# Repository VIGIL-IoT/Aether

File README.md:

# Aether

Aether is an open-source learning project with a browser-based model of two nRF24 channel selectors and a proposed KiCad carrier for an ESP32 DevKitC V4 with two nRF24 breakouts.

## Project status

| Part | Status |
| --- | --- |
| Browser simulator | Implemented. Deterministically models channel selection; emits no RF. |
| KiCad carrier R1 | Schematic and two-layer board are present and pass the recorded KiCad ERC/DRC checks. The design is unbuilt and has not been fit-checked. |
| ESP32 firmware | Legacy sketches are present but are not verified against the R1 carrier or validated on hardware. Some sketches contain RF transmission routines. |
| RF experiments | Proposals only. No measurement data or experiment results are checked in. |

The live simulator is [aether-nrf-sim.vercel.app](https://aether-nrf-sim.vercel.app/). It is the Aether app; vigil-lyart-iota.vercel.app is unrelated.

## What the simulator does

- Shows two model radios selecting among RF_CH values 0–125.
- Maps each value to a modelled centre frequency using 2400 MHz + RF_CH.
- Provides sequential, seeded-random, and fixed-offset selection modes.
- Tracks modelled visits and elapsed simulated time.
- Marks selected Wi-Fi and Bluetooth LE frequencies for reference.

The simulator does not transmit RF, scan the spectrum, generate Wi-Fi or BLE traffic, simulate packets, or measure RSSI, power, temperature, or battery state. Its outputs are deterministic software-model results.

## Architecture

```mermaid
flowchart LR
    Host["Vercel static host<br/>web/dist"] -->|static assets| UI["React browser interface<br/>controls · spectrum · history"]
    UI -->|actions| Store["In-memory simulation store"]
    Timer["Browser interval"] -->|step() while running| Store
    Store -->|current state| Model["Pure deterministic RF_CH model"]
    Model -->|next state| Store
    Store -->|subscribed snapshots| UI
    subgraph Separate["Separate repository artifacts · no runtime link"]
        Carrier["KiCad carrier R1<br/>unbuilt proposal"]
        Firmware["Legacy ESP32 firmware<br/>unvalidated"]
    end
```

See the [detailed current-system architecture](docs/architecture.md) for the component boundary and validation limits.

## Run the simulator

Requires Node.js 24 (see [.nvmrc](.nvmrc) and `web/package.json`).

    cd web
    npm ci
    npm run dev

From `web/`, run the one-command verification path:

    npm run verify

See [web/README.md](web/README.md) for controls and [docs/setup-guide.md](docs/setup-guide.md) for setup details.

For the algorithm, test method, and limits, see [methodology](docs/methodology.md). Dependency audits and on-demand SBOM generation are documented in [dependency management](docs/dependency-management.md).

## Hardware

The current carrier proposal is in [hardware/kicad/aether-carrier-r1](hardware/kicad/aether-carrier-r1/). It is powered through the ESP32 DevKit's USB input and routes its 3V3/GND and GPIO signals to two radio sockets. It has no battery, charger, USB connector, regulator, or external antenna connector.

Open the KiCad project file in that folder. Review its [README](hardware/kicad/aether-carrier-r1/README.md) and BOM before considering fabrication. The board assumes specific mating-board dimensions and pin numbering; verify the actual parts and mechanical clearances before ordering. ERC/DRC results do not establish physical fit, RF performance, or regulatory compliance.

The older files under [hardware/schematics](hardware/schematics/) and the older PCB notes are retained as legacy material and are not the R1 design.

## Safety and firmware status

The browser simulator is software-only. The legacy firmware is a separate, unvalidated codebase; it has not been reconciled with the R1 pin map, tested on hardware, or reviewed for deployment. Do not treat its presence as evidence of a safe or working radio. Review [docs/legal-and-safety.md](docs/legal-and-safety.md) before handling transmitter-capable hardware.

## Documentation

- [Documentation hub](docs/index.md)
- [Current architecture](docs/architecture.md)
- [Project scope and requirements](docs/project-scope.md)
- [Implementation methodology](docs/methodology.md)
- [Research gap and evidence needs](docs/research-gap.md)
- [Research sources](docs/research-sources.md)
- [Engineering evidence, assumptions, and FMEA-lite](docs/engineering-evidence.md)
- [Hardware references](docs/hardware-references.md)
- [Compatibility and contracts](docs/compatibility-and-contracts.md)
- [AI skills reference](docs/AI_SKILLS_REFERENCE.md)
- [Limitations](docs/limitations.md)
- [Traceability](docs/traceability.md)
- [Validation record](docs/testing-methodology.md)
- [Repository audit](docs/REPOSITORY_AUDIT.md)
- [Dependency management](docs/dependency-management.md)
- [KiCad carrier R1](hardware/kicad/aether-carrier-r1/README.md)
- [Experiments: proposals and status](experiments/README.md)
- [Security policy](SECURITY.md)
- [Web verification workflow](.github/workflows/verify-web.yml)

## Repository layout

    docs/          Project, architecture, setup, and validation documentation
    experiments/   Unexecuted experiment proposals; no result data
    firmware/      Legacy ESP32/nRF24 sketches, unvalidated against carrier R1
    hardware/      Current KiCad carrier and legacy hardware material
    web/           React/TypeScript simulator, model tests, and Vite/Vercel config

## Licensing

The repository contains a GPL-3.0 license and a CERN-OHL-S v2 hardware license. Check the relevant license file and file headers for the material you use. Firmware provenance is not fully audited; see [firmware/CHANGES.md](firmware/CHANGES.md). No license terms have been changed as part of this status correction.

## Contributing

See [CONTRIBUTING.md](CONTRIBUTING.md). Contributions should preserve the distinction between simulated output, unverified firmware, and measured hardware results.

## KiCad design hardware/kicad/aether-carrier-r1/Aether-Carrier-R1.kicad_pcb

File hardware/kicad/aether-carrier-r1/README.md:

# Aether Carrier R1

A two-layer socket carrier for one ESP32-DevKitC V4 and two nRF24L01+ breakout modules. This is a KiCad design proposal; it has not been fabricated, assembled, or physically fit-checked.

See [hardware references](../../../docs/hardware-references.md) for manufacturer constraints and [engineering evidence](../../../docs/engineering-evidence.md) for assumptions and failure modes. Exact mating-board and breakout module MPNs are not recorded.

## Files

- `Aether-Carrier-R1.kicad_pro`: KiCad project settings
- `Aether-Carrier-R1.kicad_sch`: electrical schematic
- `Aether-Carrier-R1.kicad_pcb`: routed carrier board
- `Aether.pretty/`: custom socket footprints
- `BOM.csv`: connector, passive, and mating-module list

Open the project with KiCad 10 or later. The custom footprints are loaded from the project-local `Aether.pretty` library.

## Electrical design

The carrier is powered through the ESP32 DevKit's own USB connector. The DevKit's 3V3 pin supplies both radio sockets. The carrier contains no battery, charger, USB connector, or voltage regulator. Do not power the carrier by applying an external supply to its 3V3 rail while the DevKit is connected to USB. Espressif documents the DevKitC V4 power-input options and their mutual-exclusion requirements in its [official guide](https://docs.espressif.com/projects/esp-dev-kits/en/latest/esp32/esp32-devkitc/user_guide.html).

| Radio | Bus | SCK | MOSI | MISO | CE | CSN |
|---|---|---:|---:|---:|---:|---:|
| J2 | HSPI | GPIO25 | GPIO26 | GPIO35 | GPIO32 | GPIO27 |
| J3 | VSPI | GPIO18 | GPIO23 | GPIO19 | GPIO22 | GPIO21 |

J1 uses an ESP32-DevKitC V4 2×19 header viewed from above with USB at the top: odd-numbered pins are on the left and even-numbered pins are on the right. Unused DevKit pins have explicit no-connect markers. J1 pins 1, 2, 14, and 27 provide 3V3/GND connections as shown in the schematic.

J2 and J3 use the common numbered nRF24L01+ 2×4 module header:

| Pin | Signal | Pin | Signal |
|---:|---|---:|---|
| 1 | GND | 2 | VCC (3V3) |
| 3 | CE | 4 | CSN |
| 5 | SCK | 6 | MOSI |
| 7 | MISO | 8 | IRQ (NC) |

The socket footprints mark pin 1 with a square pad. Module and adapter vendors can change the board layout or labels; verify the specific mating module's pinout and orientation before inserting it or applying power. Pin 8 IRQ is intentionally unconnected because the carrier's current signal map does not use radio interrupts. The [RF24 library documentation](https://github.com/nRF24/RF24/blob/master/docs/main_page.md) lists the conventional module header signals.

C1/C3 are 10 µF 1206 capacitors and C2/C4 are 100 nF 0805 capacitors, one pair beside each radio socket. Their values and placement are design choices for this untested prototype, not measured power-integrity results.

## Board and fabrication notes

- Outline: 73.66 × 71.12 mm
- Two copper layers; bottom GND zone and local ground stitching
- Signal tracks: 0.30 mm; 3V3/GND tracks: 0.50 mm
- Plated vias: 0.60 mm pad / 0.30 mm drill
- Custom ESP32 socket assumes 2.54 mm pin pitch and 25.4 mm row spacing
- Radio sockets assume a 2×4, 2.54 mm male header

The ESP32 socket assumes a DevKitC V4-sized board and matching male headers. Clones can differ in header spacing, USB connector placement, and board outline. The 3D preview does not model the mating DevKit or radio modules. Check the exact parts, underside clearance, connector height, enclosure, and socket fit before ordering a board. No Gerbers, assembly drawings, or manufacturing outputs are included in this revision.

## Checks run

Using KiCad CLI 10.0.7:

```sh
kicad-cli sch erc --exit-code-violations --output erc.rpt Aether-Carrier-R1.kicad_sch
kicad-cli pcb drc --refill-zones --save-board --all-track-errors --schematic-parity --output drc.rpt Aether-Carrier-R1.kicad_pcb
```

The checked-in design reported 0 ERC violations, 0 PCB DRC violations, 0 unconnected items, and 0 schematic-parity issues. These checks cover KiCad's electrical/routing rules; they do not verify connector fit, thermal performance, signal integrity, radio behavior, or regulatory compliance.

## BOM

See [BOM.csv](BOM.csv). The mating development boards and radio breakouts are not fitted to the carrier PCB.

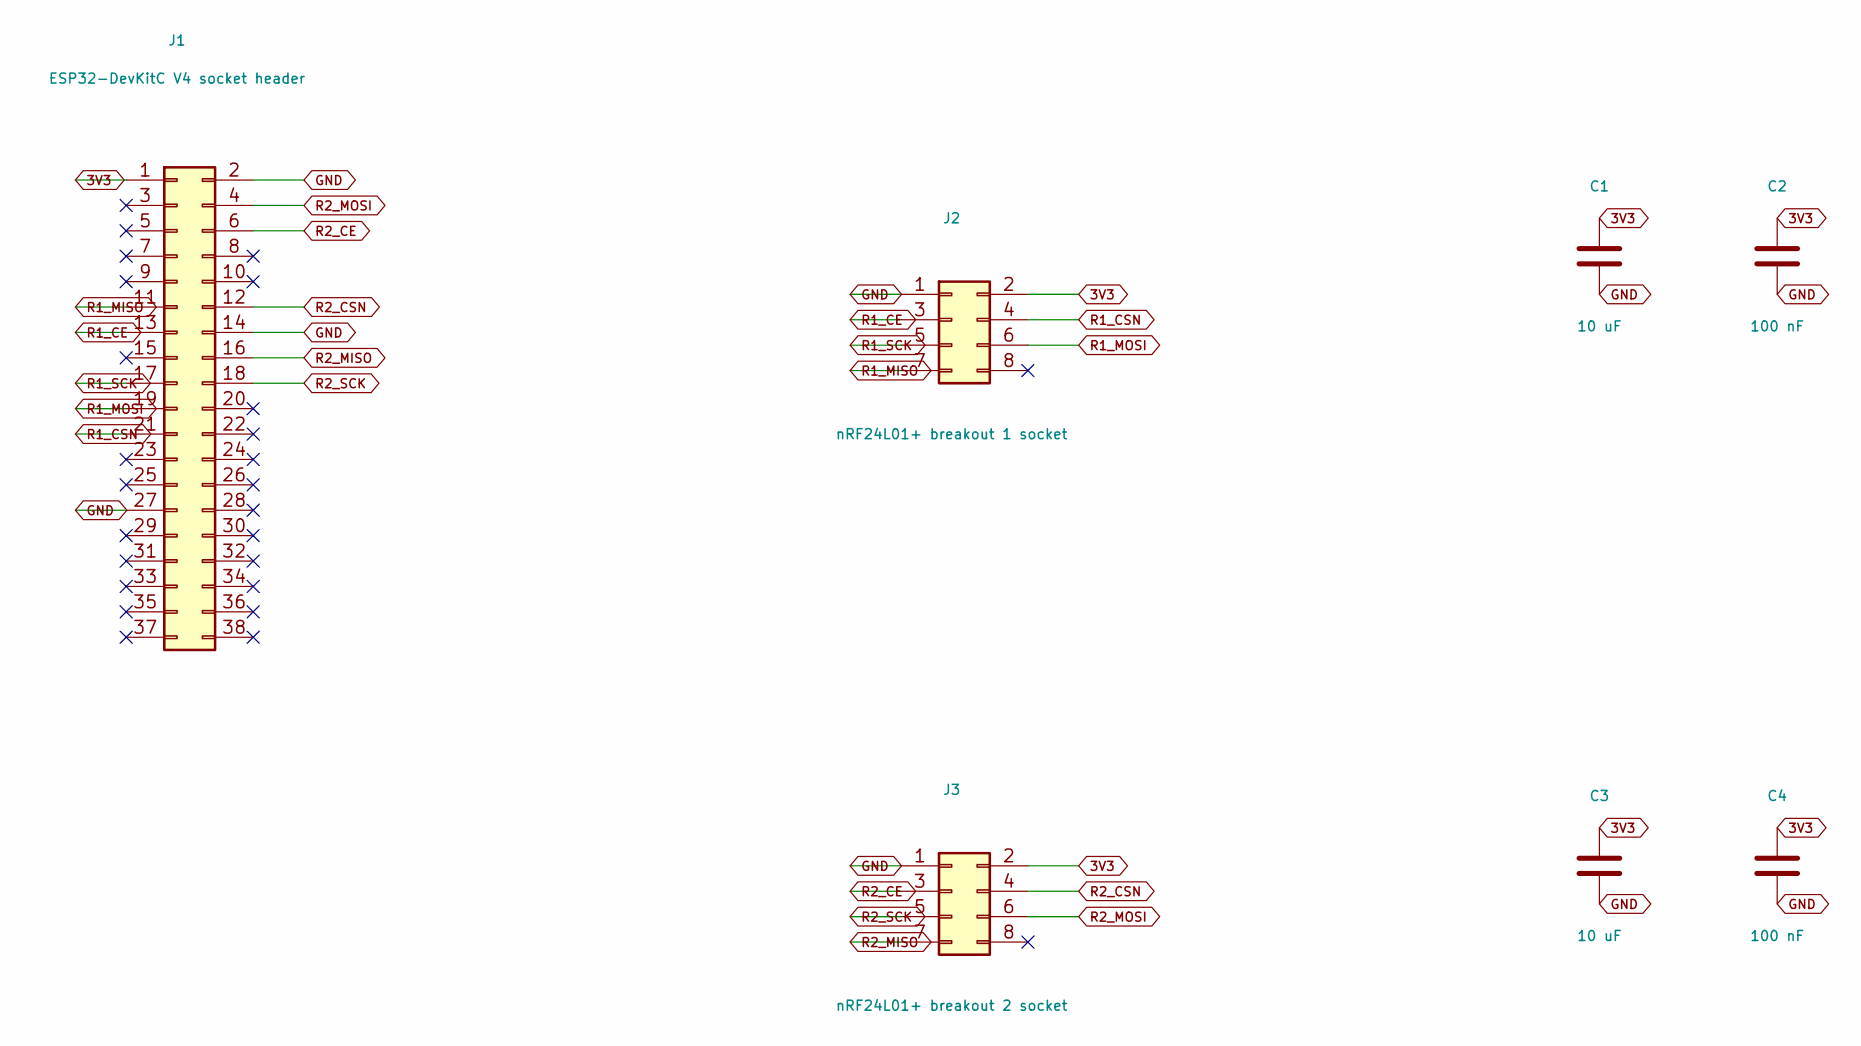
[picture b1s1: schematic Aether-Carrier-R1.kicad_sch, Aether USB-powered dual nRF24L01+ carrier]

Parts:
C1, C3: 10 uF; C_1206_3216Metric
C2, C4: 100 nF; C_0805_2012Metric
J1: ESP32-DevKitC V4 socket header; ESP32-DevKitC-V4_2x19_Socket
J2: nRF24L01+ breakout 1 socket; nRF24L01_Breakout_2x4_Socket
J3: nRF24L01+ breakout 2 socket; nRF24L01_Breakout_2x4_Socket

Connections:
3V3: C1.1, C2.1, C3.1, C4.1, J1.1, J2.2, J3.2
GND: C1.2, C2.2, C3.2, C4.2, J1.2, J1.14, J1.27, J2.1, J3.1
R1_CE: J1.13, J2.3
R1_CSN: J1.21, J2.4
R1_MISO: J1.11, J2.7
R1_MOSI: J1.19, J2.6
R1_SCK: J1.17, J2.5
R2_CE: J1.6, J3.3
R2_CSN: J1.12, J3.4
R2_MISO: J1.16, J3.7
R2_MOSI: J1.4, J3.6
R2_SCK: J1.18, J3.5

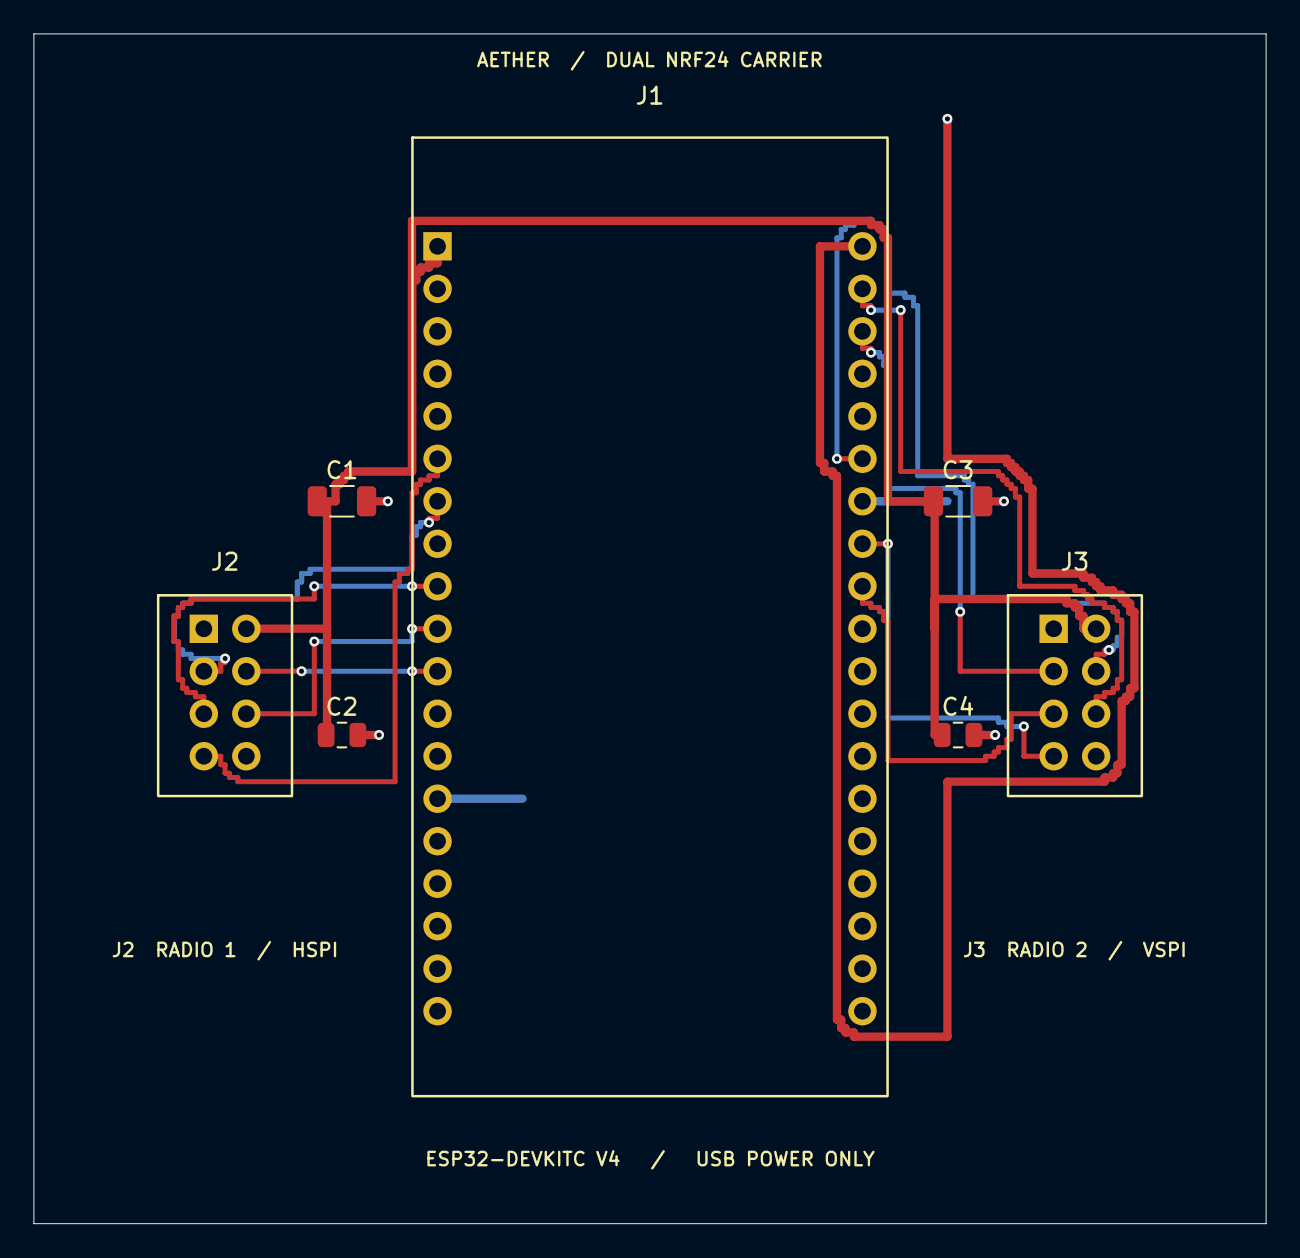
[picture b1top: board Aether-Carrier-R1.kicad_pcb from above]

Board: 2 copper layers, 73.7 x 71.1 mm, 7 parts (0 on the bottom side), 12 nets.

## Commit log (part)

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2026-05-11 feat: initial HopShift repository skeleton
2026-05-11 docs: improve README introduction with welcoming tone
2026-05-11 fix: formatting fix for markdowns
2026-05-12 refactor: rename project from HopShift to Aether
2026-05-12 docs: add polished name origin section for Aether
2026-05-12 fix: replace all HopShift references with Aether and remove em dashes
2026-05-14 change Security Link
2026-05-15 Update LICENSE to CERN
2026-05-29 Add ESP32 NRF24L01+ example sketches and credit source repository
2026-05-30 Expand repository with comprehensive RF engineering documentation and experiment framework
2026-05-30 Add block diagram as README cover image
2026-05-30 Add authentic design journal documenting learning journey and design decisions
2026-05-30 Fix grammatical punctuation in design journal
2026-05-30 Update design journal timestamp to May 30, 2026
2026-05-30 remove .gitkeep from assets
2026-05-31 Reorganize assets: move block diagram to images folder and update README
2026-05-31 Fix licensing and attribution: GPL v3 for firmware, proper credits to smoochiee/Ble-jammer
2026-05-31 Fix LICENSE-HARDWARE: replace GPL v3 with correct CERN-OHL-S v2 license text
2026-05-31 Update README cover image to new Aether Cover Image
2026-05-31 Remove render folder
2026-05-31 Complete documentation structure refactoring
    - Streamlined README.md to concise landing page (300-400 lines)
    - Added professional badges and navigation links
    - Created comprehensive assembly guide with step-by-step instructions
    - Added detailed power budget analysis with battery life calculations
    - Created cost analysis for different build configurations
    - Added build variants documentation for various use cases
2026-06-01 added iteration 1 schematics and component list
2026-06-01 Iteration 1 -> Iteration 1.1
    connected ground pins and minor connections done with antenna and development board
2026-06-01 added web simulation for Aether
2026-06-01 feat: configure Aether simulator for Vercel deployment
    - Add complete package.json with React, TypeScript, TailwindCSS, Framer Motion, Zustand
    - Fix malformed index.html
    - Enhance vite.config.ts with build optimization
    - Create vercel.json for Vercel build configuration
    - Add .nvmrc for Node.js version pinning (18.17.0)
    - Fix OccupancyMap grid layout to use inline styles
2026-06-01 fix: use npm --prefix for Vercel build command
    Replace 'cd web' with 'npm --prefix web' to work in Vercel's build environment
2026-06-01 fix: correct npm prefix path for Vercel build
2026-06-01 fix: use bash build script for Vercel
2026-06-01 fix: use inline cd command in vercel.json build
2026-06-01 fix: use subshell syntax for cd in vercel build
2026-06-01 trigger: retry Vercel deployment with subshell cd
2026-06-01 fix: remove unused currentExperiment variable
2026-06-01 fix: add terser as devDependency for Vite minification
2026-06-02 feat: make text unselectable and add GitHub button to footer
2026-06-16 docs: add ESP32 learning resource to setup guide
